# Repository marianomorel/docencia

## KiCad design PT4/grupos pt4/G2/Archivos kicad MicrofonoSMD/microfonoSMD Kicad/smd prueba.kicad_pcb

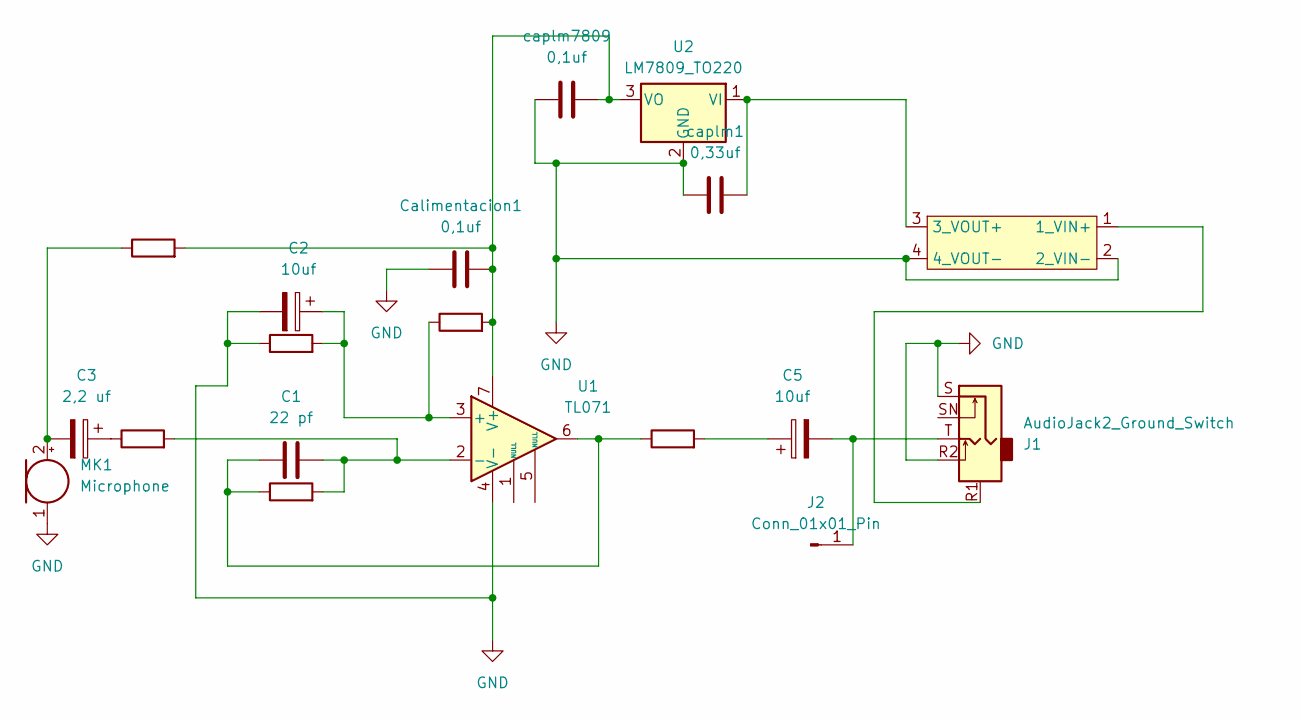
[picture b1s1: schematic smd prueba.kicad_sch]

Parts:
C1: 22 pf; C_0805_2012Metric_Pad1.18x1.45mm_HandSolder
C2, C5: 10uf; CP_Elec_4x5.4
C3: 2,2 uf; CP_Elec_4x5.4
Calimentacion1: 0,1uf; C_0805_2012Metric_Pad1.18x1.45mm_HandSolder
J1: AudioJack2_Ground_Switch; Jack_3.5mm_PJ320D_Horizontal
J2: Conn_01x01_Pin; PinHeader_1x01_P1.00mm_Vertical
MK1: Microphone; POM-2244P-C3310-2-R
R3: 2,2k; R_1206_3216Metric_Pad1.30x1.75mm_HandSolder
R5: 100; R_1206_3216Metric_Pad1.30x1.75mm_HandSolder
RP2: 200k; R_1206_3216Metric_Pad1.30x1.75mm_HandSolder
RP3: 10k; R_1206_3216Metric_Pad1.30x1.75mm_HandSolder
Ralimentacion1: 10k; R_1206_3216Metric_Pad1.30x1.75mm_HandSolder
Rpolarizadordeelectret1: 10k; R_1206_3216Metric_Pad1.30x1.75mm_HandSolder
U1: TL071; soic 8 personalizado
U2: LM7809_TO220; TO-252-2
U3: modulo mt3608
caplm1: 0,33uf; C_0805_2012Metric_Pad1.18x1.45mm_HandSolder
caplm7809: 0,1uf; C_0805_2012Metric_Pad1.18x1.45mm_HandSolder

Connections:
GND: C2.2, Calimentacion1.1, J1.R2, J1.S, MK1.1 (-), RP3.1, U1.4 (V-), U2.2 (GND), U3.2 (2_VIN-), U3.4 (4_VOUT-), caplm1.1, caplm7809.1
unnamed: C1.2, R5.1, RP2.1, U1.6
unnamed: C3.1, R3.1
unnamed: C5.1, R5.2
unnamed: C5.2, J1.T, J2.1
unnamed: C3.2, MK1.2 (+), Rpolarizadordeelectret1.1
unnamed: C2.1, RP3.2, Ralimentacion1.1, U1.3 (+)
unnamed: C1.1, R3.2, RP2.2, U1.2 (-)
unnamed: Calimentacion1.2, Ralimentacion1.2, Rpolarizadordeelectret1.2, U1.7 (V+), U2.3 (VO), caplm7809.2
unnamed: U2.1 (VI), U3.3 (3_VOUT+), caplm1.2
unnamed: J1.R1, U3.1 (1_VIN+)

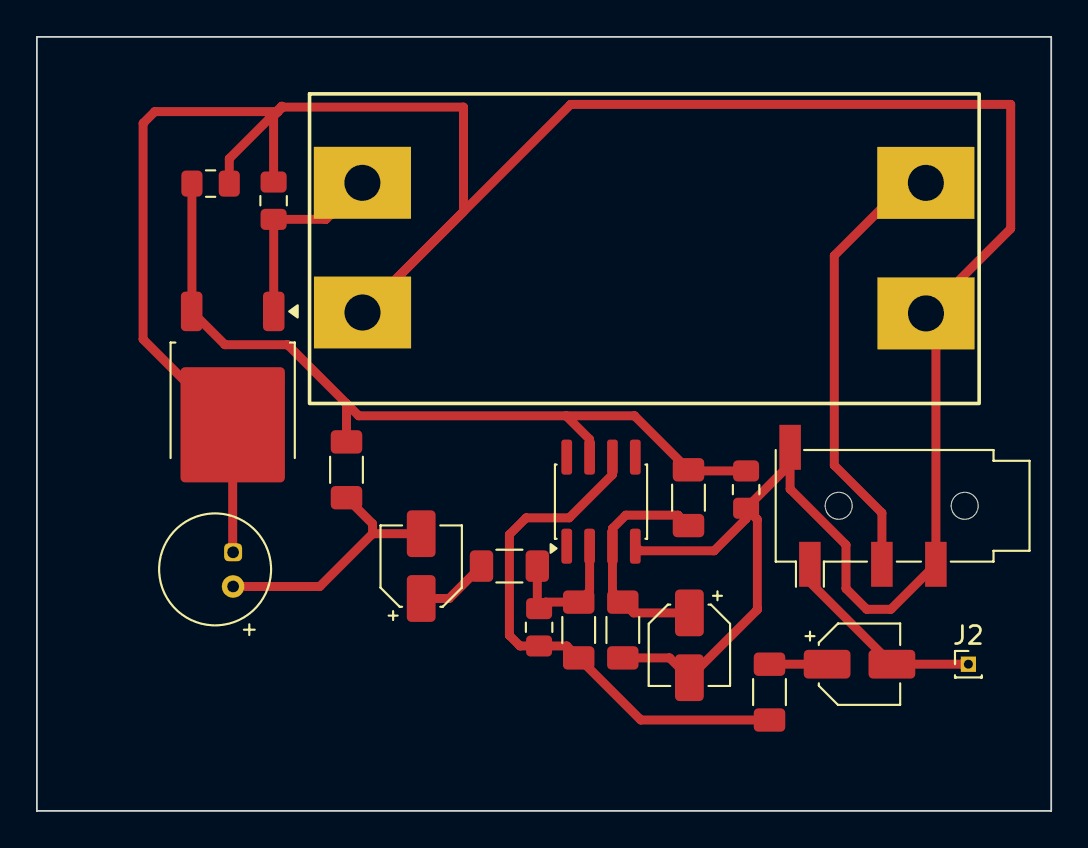
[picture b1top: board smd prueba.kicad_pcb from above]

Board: 2 copper layers, 56.3 x 43.0 mm, 19 parts (0 on the bottom side), 11 nets.

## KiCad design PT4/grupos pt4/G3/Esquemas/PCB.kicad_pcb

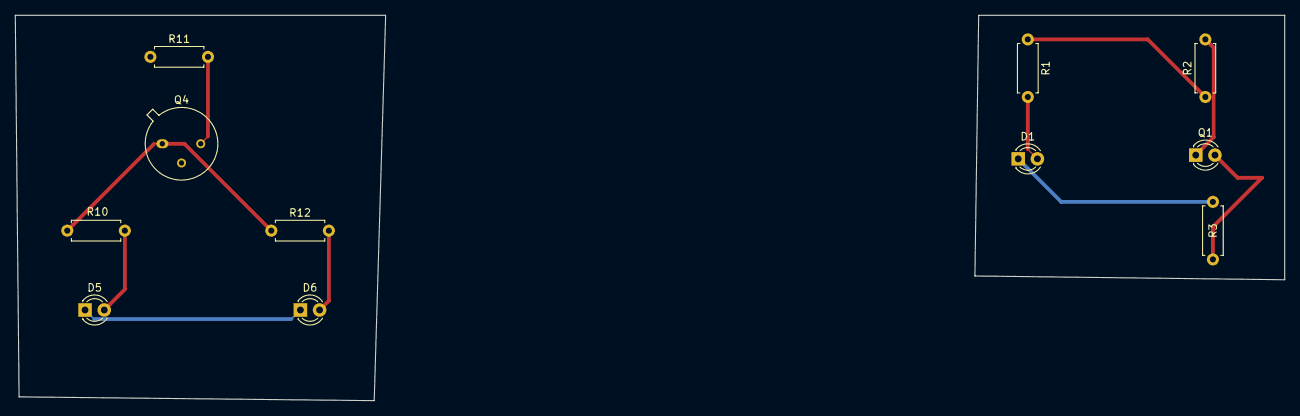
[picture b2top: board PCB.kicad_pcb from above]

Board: 2 copper layers, 168.0 x 51.0 mm, 11 parts (0 on the bottom side), 9 nets.

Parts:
D1, D5, D6: IR204A; LED_D3.0mm_IRBlack
Q1: TEPT4400; LED_D3.0mm_Clear
Q4: 2N2219; TO-39-3
R1, R2, R10, R12: 220; R_Axial_DIN0207_L6.3mm_D2.5mm_P7.62mm_Horizontal
R3, R11: 10k; R_Axial_DIN0207_L6.3mm_D2.5mm_P7.62mm_Horizontal

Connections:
+5V: R1.1, R2.1, R11.1
GND: D1.1 (K), D5.1 (K), D6.1 (K), R3.2
unnamed: Q1.2 (E), R3.1
unnamed: D1.2 (A), R1.2
unnamed: D5.2 (A), R10.2
unnamed: D6.2 (A), R12.2
unnamed: Q1.1 (C), R2.2
unnamed: Q4.3 (C), R11.2
unnamed: Q4.1 (E), R10.1, R12.1

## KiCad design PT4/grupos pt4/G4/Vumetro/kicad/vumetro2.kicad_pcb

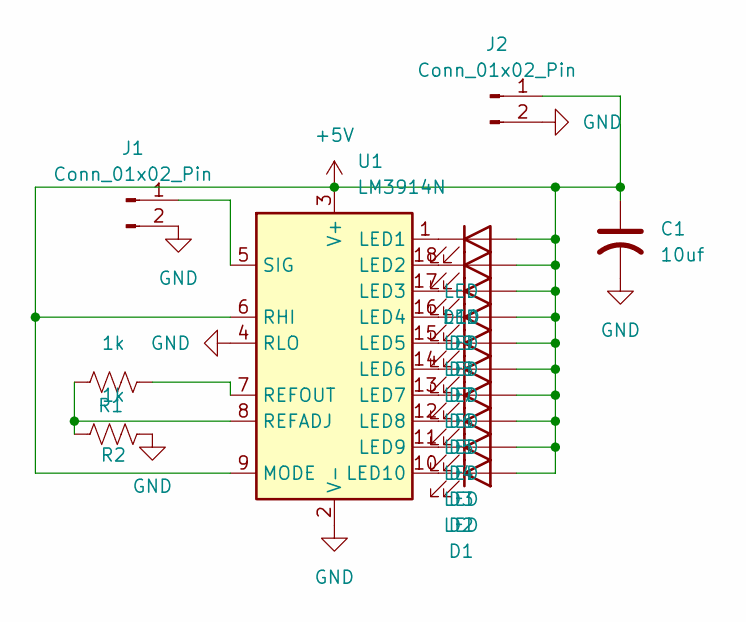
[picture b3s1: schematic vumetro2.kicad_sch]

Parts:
C1: 10uf; CP_Radial_D5.0mm_P2.00mm
D1, D2, D3, D4, D5, D6, D7, D8, D9, D10: LED; LED_D3.0mm_FlatTop
J1, J2: Conn_01x02_Pin; TerminalBlock_4Ucon_1x02_P3.50mm_Horizontal
R1, R2: 1k; R_Axial_DIN0204_L3.6mm_D1.6mm_P5.08mm_Horizontal
U1: LM3914N; DIP-18_W7.62mm

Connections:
+5V: C1.1, D1.2 (A), D2.2 (A), D3.2 (A), D4.2 (A), D5.2 (A), D6.2 (A), D7.2 (A), D8.2 (A), D9.2 (A), D10.2 (A), J2.1, U1.3 (V+), U1.6 (RHI), U1.9 (MODE)
GND: C1.2, J1.2, J2.2, R2.2, U1.2 (V-), U1.4 (RLO)
unnamed: D1.1 (K), U1.10 (LED10)
unnamed: D2.1 (K), U1.11 (LED9)
unnamed: D3.1 (K), U1.12 (LED8)
unnamed: D4.1 (K), U1.13 (LED7)
unnamed: D5.1 (K), U1.14 (LED6)
unnamed: D6.1 (K), U1.15 (LED5)
unnamed: D7.1 (K), U1.16 (LED4)
unnamed: D8.1 (K), U1.17 (LED3)
unnamed: D9.1 (K), U1.18 (LED2)
unnamed: D10.1 (K), U1.1 (LED1)
unnamed: J1.1, U1.5 (SIG)
unnamed: R1.1, R2.1, U1.8 (REFADJ)
unnamed: R1.2, U1.7 (REFOUT)

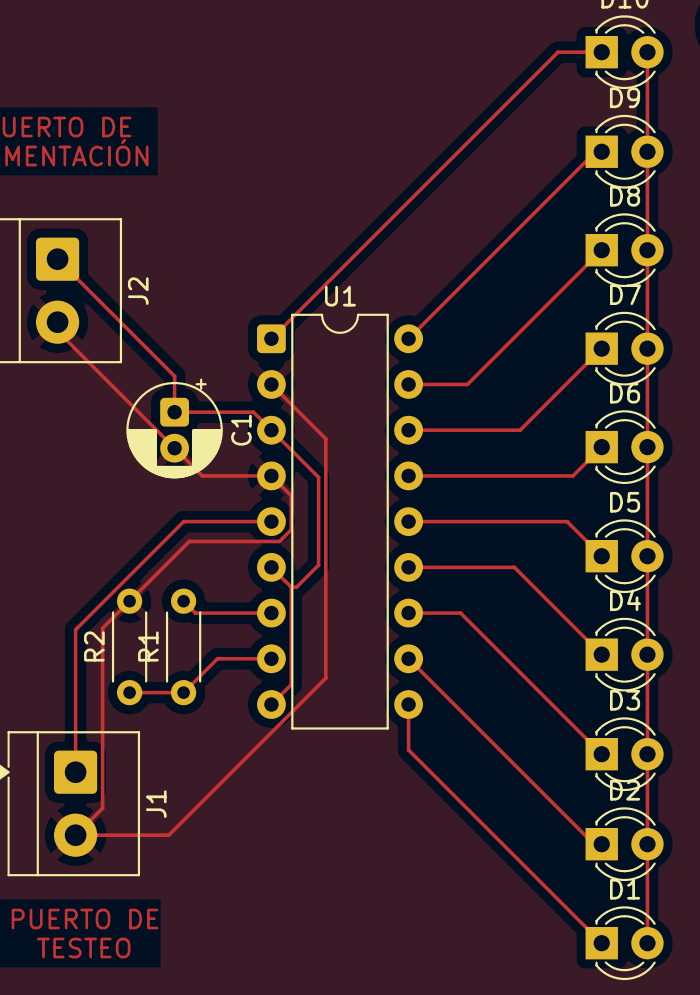
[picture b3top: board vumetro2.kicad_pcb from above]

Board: 2 copper layers, 16 parts (0 on the bottom side), 15 nets.

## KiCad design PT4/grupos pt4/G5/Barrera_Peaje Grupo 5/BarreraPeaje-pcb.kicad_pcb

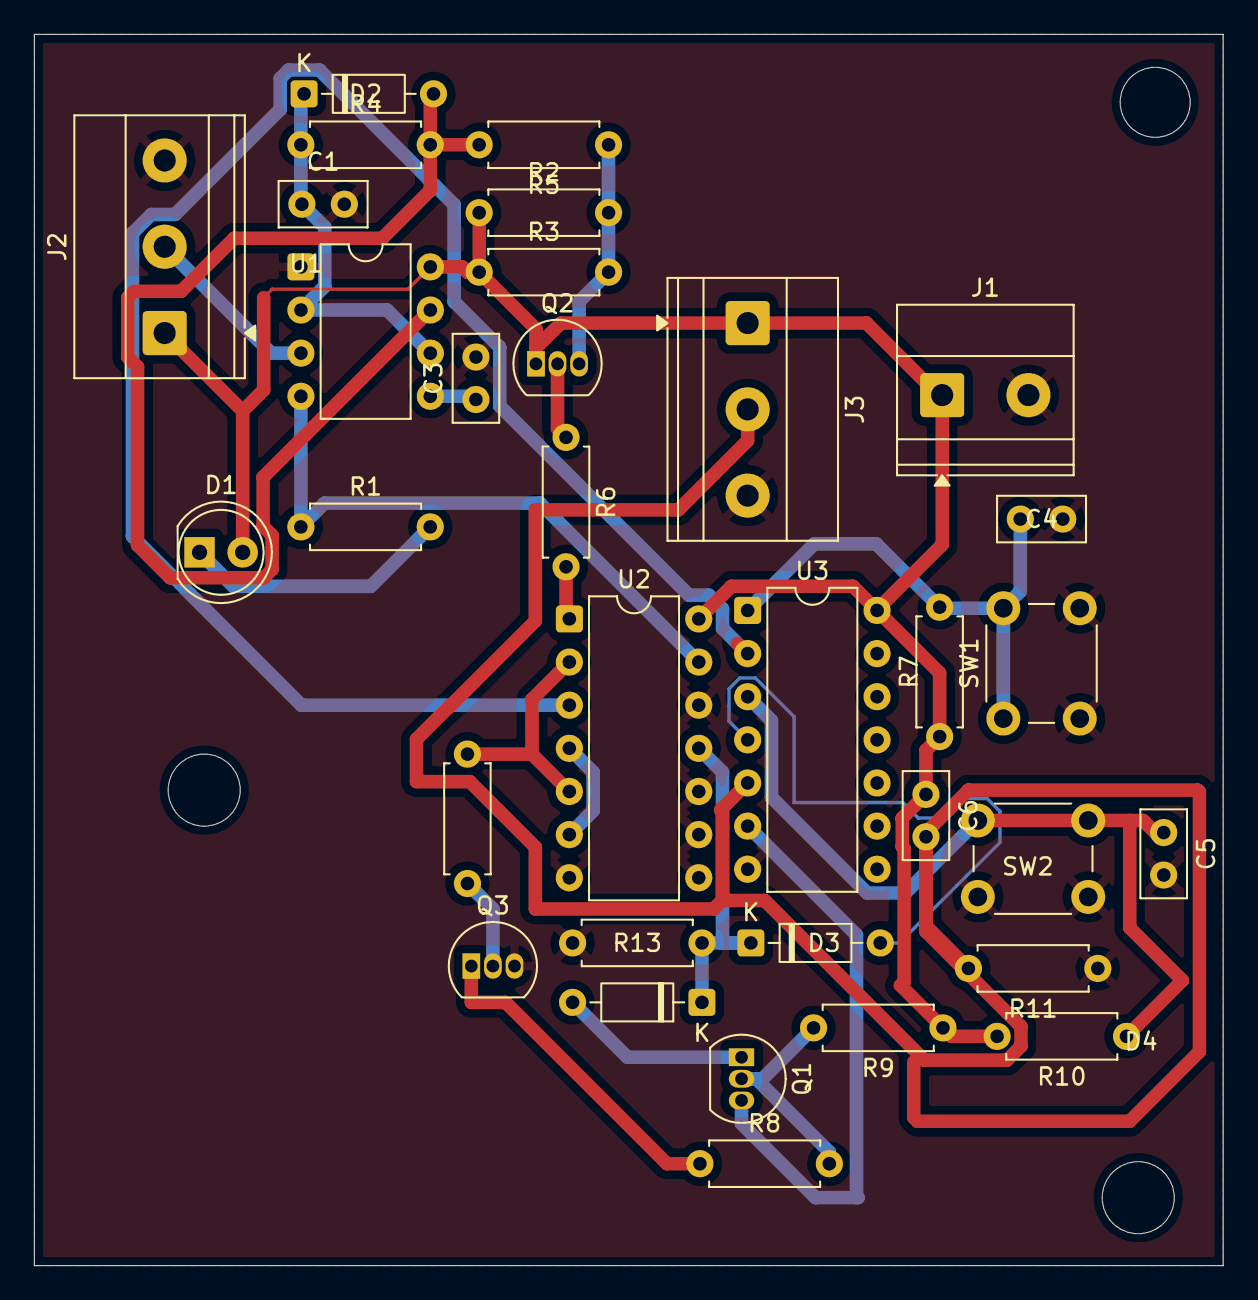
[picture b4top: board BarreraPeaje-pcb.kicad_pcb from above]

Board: 2 copper layers, 70.0 x 72.5 mm, 33 parts (0 on the bottom side), 24 nets.

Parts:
C1: 10nF; C_Disc_D5.0mm_W2.5mm_P2.50mm
C3, C4, C5, C6: 100nF; C_Disc_D5.0mm_W2.5mm_P2.50mm
D1: LED; LED_D5.0mm
D2, D3, D4: 1N4148; D_DO-35_SOD27_P7.62mm_Horizontal
J1: Alimentacion 12V; TerminalBlock_Phoenix_MKDS-1,5-2-5.08_1x02_P5.08mm_Horizont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
J2: Salida/Servo; TerminalBlock_Phoenix_MKDS-1,5-3-5.08_1x03_P5.08mm_Horizont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
J3: Sensor en Barrera; TerminalBlock_Phoenix_MKDS-1,5-3-5.08_1x03_P5.08mm_Horizont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
Q1: BC558; TO-92_Inline
Q2, Q3: BC548; TO-92_Inline
R1, R6, R7, R10, R11, R13: 10k; R_Axial_DIN0207_L6.3mm_D2.5mm_P7.62mm_Horizontal
R2: 47k; R_Axial_DIN0207_L6.3mm_D2.5mm_P7.62mm_Horizontal
R3, R9: 15k; R_Axial_DIN0207_L6.3mm_D2.5mm_P7.62mm_Horizontal
R4: 270k; R_Axial_DIN0207_L6.3mm_D2.5mm_P7.62mm_Horizontal
R5: 180; R_Axial_DIN0207_L6.3mm_D2.5mm_P7.62mm_Horizontal
R8, R12: 1k; R_Axial_DIN0207_L6.3mm_D2.5mm_P7.62mm_Horizontal
SW1: Open/Close; SW_PUSH_6mm_H4.3mm
SW2: Marcha/Stop; SW_PUSH_6mm_H4.3mm
U1: LM555xN; DIP-8_W7.62mm
U2: 4013; DIP-14_W7.62mm
U3: 40106; DIP-14_W7.62mm

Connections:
+5V: C6.1, D1.2 (A), J1.1, J2.1, J3.1, Q2.1 (C), R2.1, R3.1, R7.1, R9.1, R10.2, U1.8 (VCC), U2.14 (VDD), U3.14 (VDD)
GND: C1.2, C3.2, C4.2, C5.2, J1.2, J2.3, J3.3, Q3.3 (E), R11.1, R13.2, SW1.2, SW2.1, U1.1 (GND), U2.7 (VSS), U2.8 (S), U2.9 (D), U2.10 (R), U2.12 (~Q), U3.7 (VSS)
unnamed: C4.1, R7.2, SW1.1, U3.1
unnamed: C5.1, R10.1, SW2.2, U3.3
unnamed: D1.1 (K), R1.2
unnamed: D2.2 (A), R4.2, R5.2, U1.7 (DIS)
unnamed: C1.1, D2.1 (K), R4.1, U1.2 (TR), U1.6 (THR)
unnamed: D3.2 (A), U3.4
unnamed: D3.1 (K), D4.1 (K), R13.1, U2.11 (C)
unnamed: D4.2 (A), Q1.1 (C)
unnamed: J2.2, U1.3 (Q)
unnamed: C6.2, J3.2, R11.2, U3.5
unnamed: Q1.2 (B), R8.2, R9.2
unnamed: Q1.3 (E), U3.6
unnamed: Q2.2 (B), R6.1
unnamed: Q2.3 (E), R2.2, R3.2, R5.1
unnamed: Q3.2 (B), R12.2
unnamed: Q3.1 (C), R8.1
unnamed: C3.1, U1.5 (CV)
unnamed: R1.1, U1.4 (R), U2.13 (Q)
unnamed: U2.3 (C), U3.2
unnamed: R12.1, U2.2 (~Q), U2.5 (D)
unnamed: R6.2, U2.1 (Q)
unnamed: U2.4 (R), U2.6 (S)

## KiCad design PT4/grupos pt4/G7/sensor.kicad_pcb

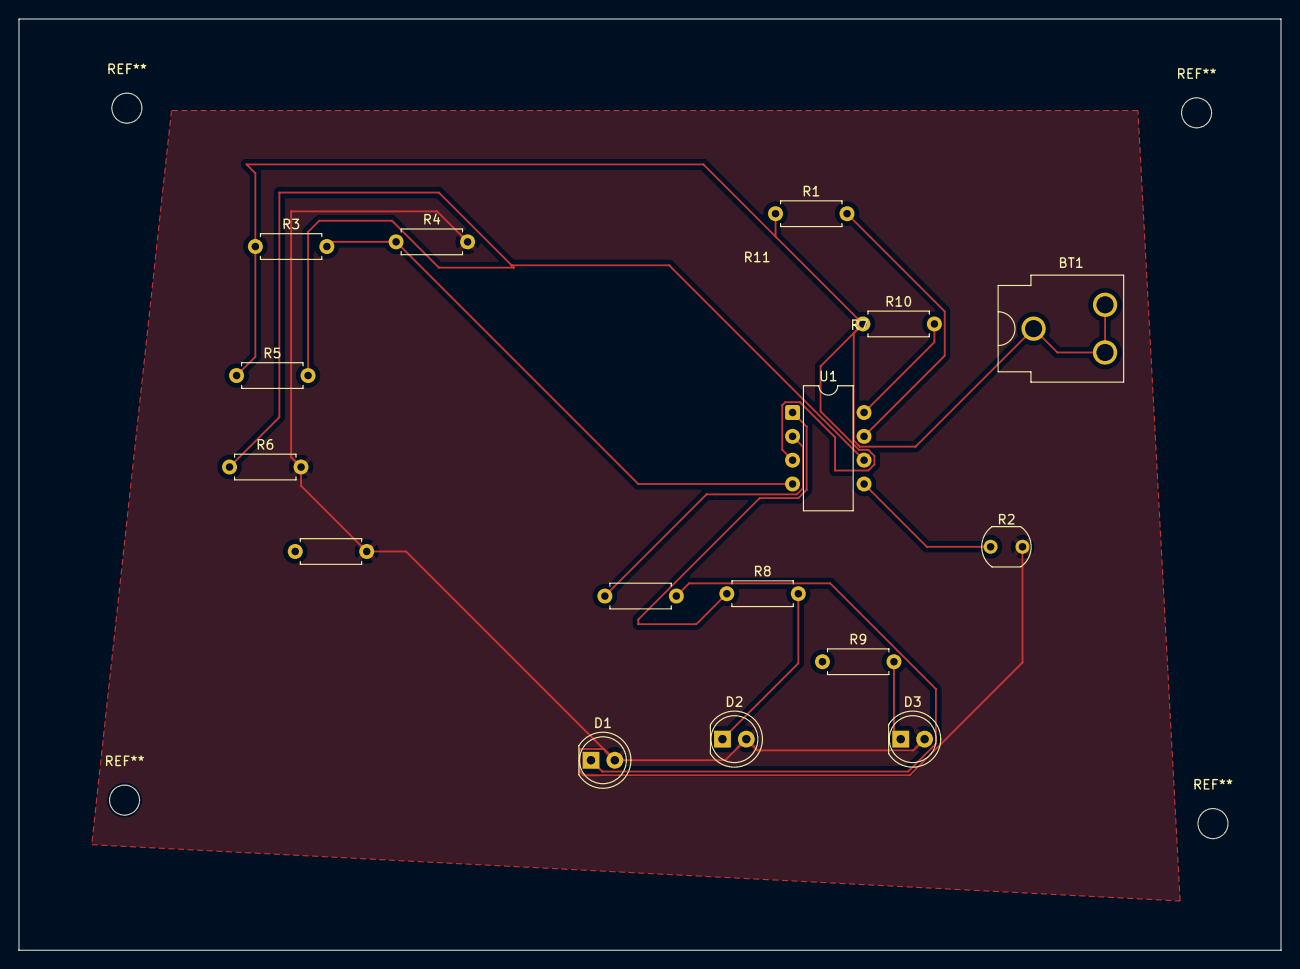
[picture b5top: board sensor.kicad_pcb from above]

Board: 2 copper layers, 134.5 x 99.2 mm, 16 parts (0 on the bottom side), 11 nets.

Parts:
BT1: Battery; BatteryClip_Keystone_54_D16-19mm
D1, D2, D3: LED; LED_D5.0mm
R1, R3, R4, R5, R6, R7, R8, R9, R10, R11: R; R_Axial_DIN0207_L6.3mm_D2.5mm_P7.62mm_Horizontal
R2: LDR07; R_LDR_5.1x4.3mm_P3.4mm_Vertical
U1: LM339; CERDIP-8_W7.62mm_SideBrazed

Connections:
Earth: D1.2 (A), D2.2 (A), D3.2 (A), R2.2, R4.2, R6.2, R11.2
unnamed: BT1.1 (+), R1.1, R3.1, R5.1, R10.1, U1.3 (V+)
unnamed: D1.1 (K), R7.2
unnamed: D2.1 (K), R8.2
unnamed: D3.1 (K), R9.2
unnamed: R7.1, U1.2
unnamed: R8.1, U1.1
unnamed: R1.2, R2.1, U1.5 (+), U1.7 (+)
unnamed: R3.2, R4.1, U1.4 (-)
unnamed: R5.2, R6.1, U1.6 (-)
unnamed: R10.2, U1.8 (-)

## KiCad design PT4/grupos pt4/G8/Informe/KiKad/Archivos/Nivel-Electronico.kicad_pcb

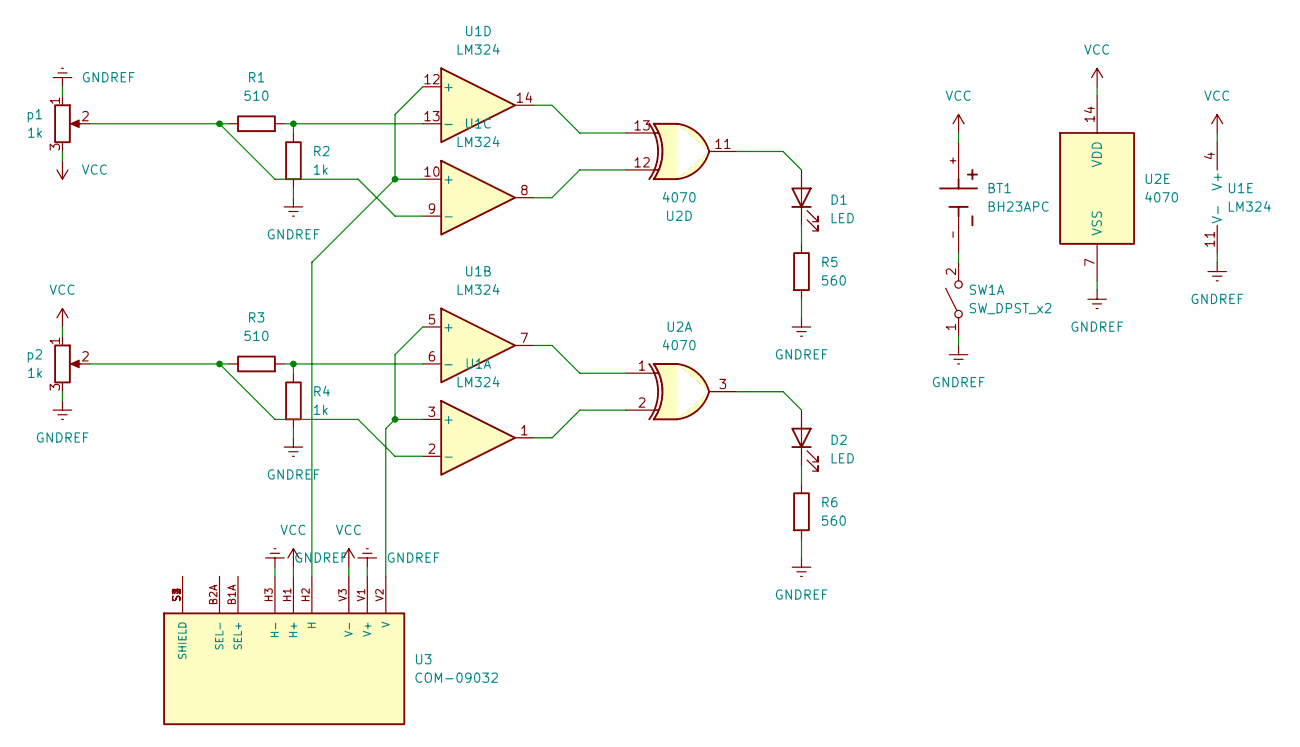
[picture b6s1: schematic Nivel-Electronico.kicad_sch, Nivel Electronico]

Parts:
BT1: BH23APC; BAT_BH23APC
D1, D2: LED; LED_D5.0mm
R1, R3: 510; R_Axial_DIN0204_L3.6mm_D1.6mm_P5.08mm_Vertical
R2, R4: 1k; R_Axial_DIN0204_L3.6mm_D1.6mm_P5.08mm_Vertical
R5, R6: 560; R_Axial_DIN0204_L3.6mm_D1.6mm_P5.08mm_Vertical
SW1: SW_DPST_x2; SW_Push_2P2T_Toggle_CK_PVA2OAH5xxxxxxV2
U1: LM324; DIP-14_W7.62mm_LongPads
U2: 4070; DIP-14_W7.62mm_LongPads
U3: COM-09032; XDCR_COM-09032
p1, p2: 1k; Potentiometer_ACP_CA9-V10_Vertical

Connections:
GNDREF: R2.2, R4.2, R5.2, R6.2, SW1.1 (A), U1.11 (V-), U2.7 (VSS), U3.H3 (H-), U3.V1 (V+), p1.1, p2.3
unnamed: D1.2 (A), U2.11
unnamed: D1.1 (K), R5.1
unnamed: D2.2 (A), U2.3
unnamed: D2.1 (K), R6.1
unnamed: BT1.-, SW1.2 (B)
unnamed: U1.1, U2.2
unnamed: U1.7, U2.1
unnamed: U1.8, U2.12
unnamed: U1.14, U2.13
unnamed: U1.3 (+), U1.5 (+), U3.V2 (V)
unnamed: R3.1, U1.2 (-), p2.2
unnamed: R3.2, R4.1, U1.6 (-)
unnamed: U1.10 (+), U1.12 (+), U3.H2 (H)
unnamed: R1.1, U1.9 (-), p1.2
unnamed: R1.2, R2.1, U1.13 (-)
unnamed: U3.S1 (SHIELD), U3.S2 (SHIELD), U3.S3 (SHIELD), U3.S4 (SHIELD)
VCC: BT1.+, U1.4 (V+), U2.14 (VDD), U3.H1 (H+), U3.V3 (V-), p1.3, p2.1

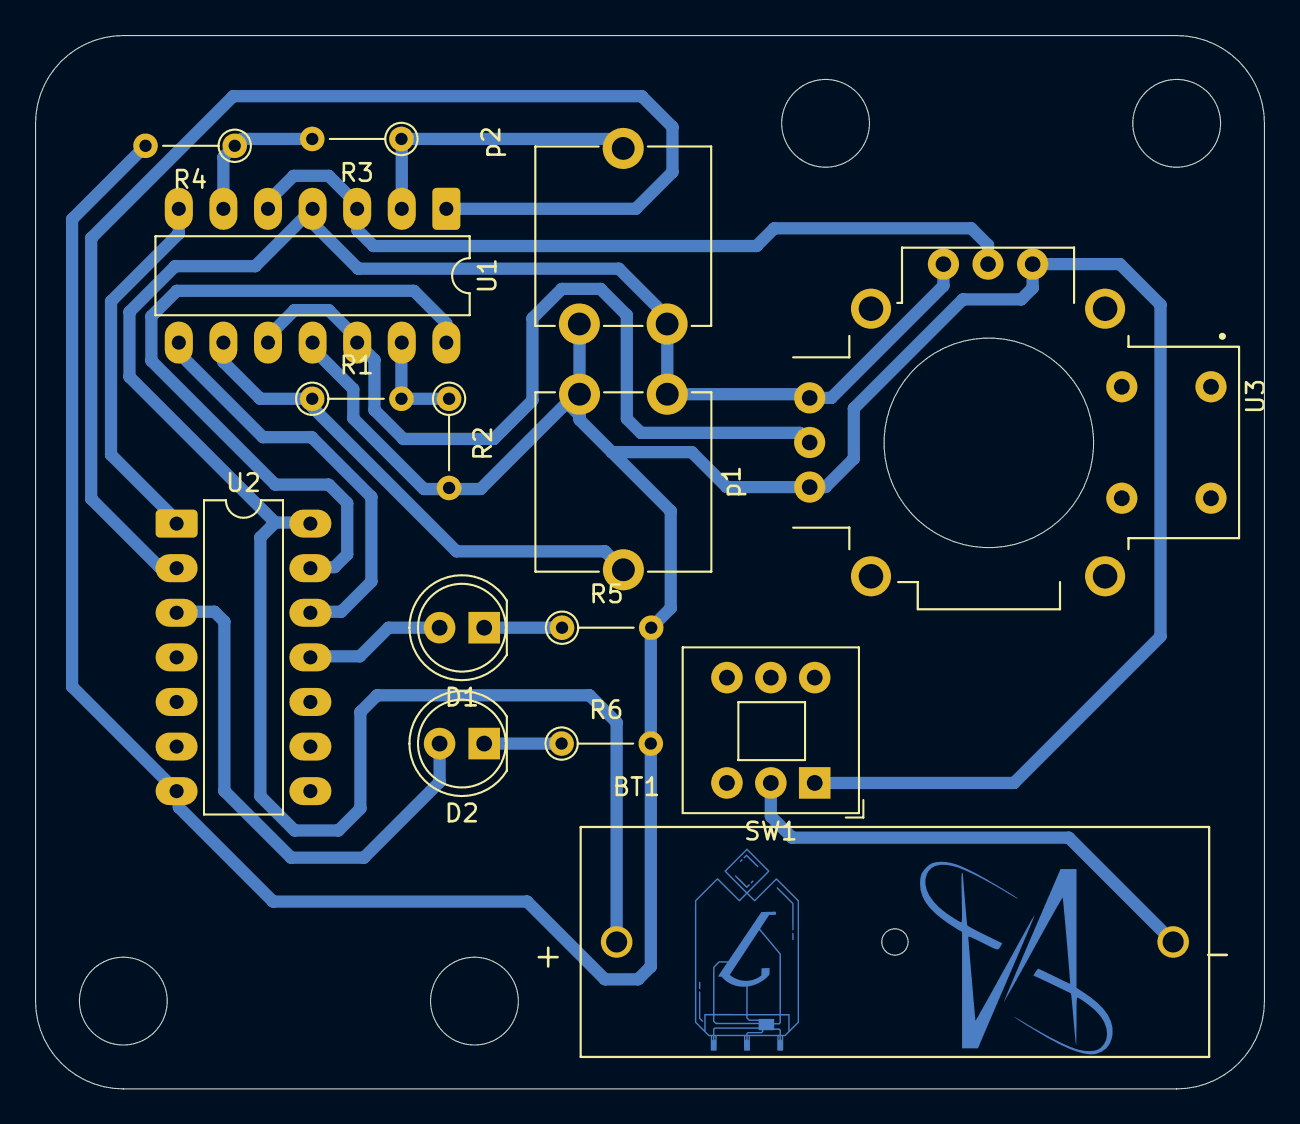
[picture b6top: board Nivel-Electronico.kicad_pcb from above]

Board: 2 copper layers, 70.0 x 60.0 mm, 15 parts (0 on the bottom side), 18 nets.

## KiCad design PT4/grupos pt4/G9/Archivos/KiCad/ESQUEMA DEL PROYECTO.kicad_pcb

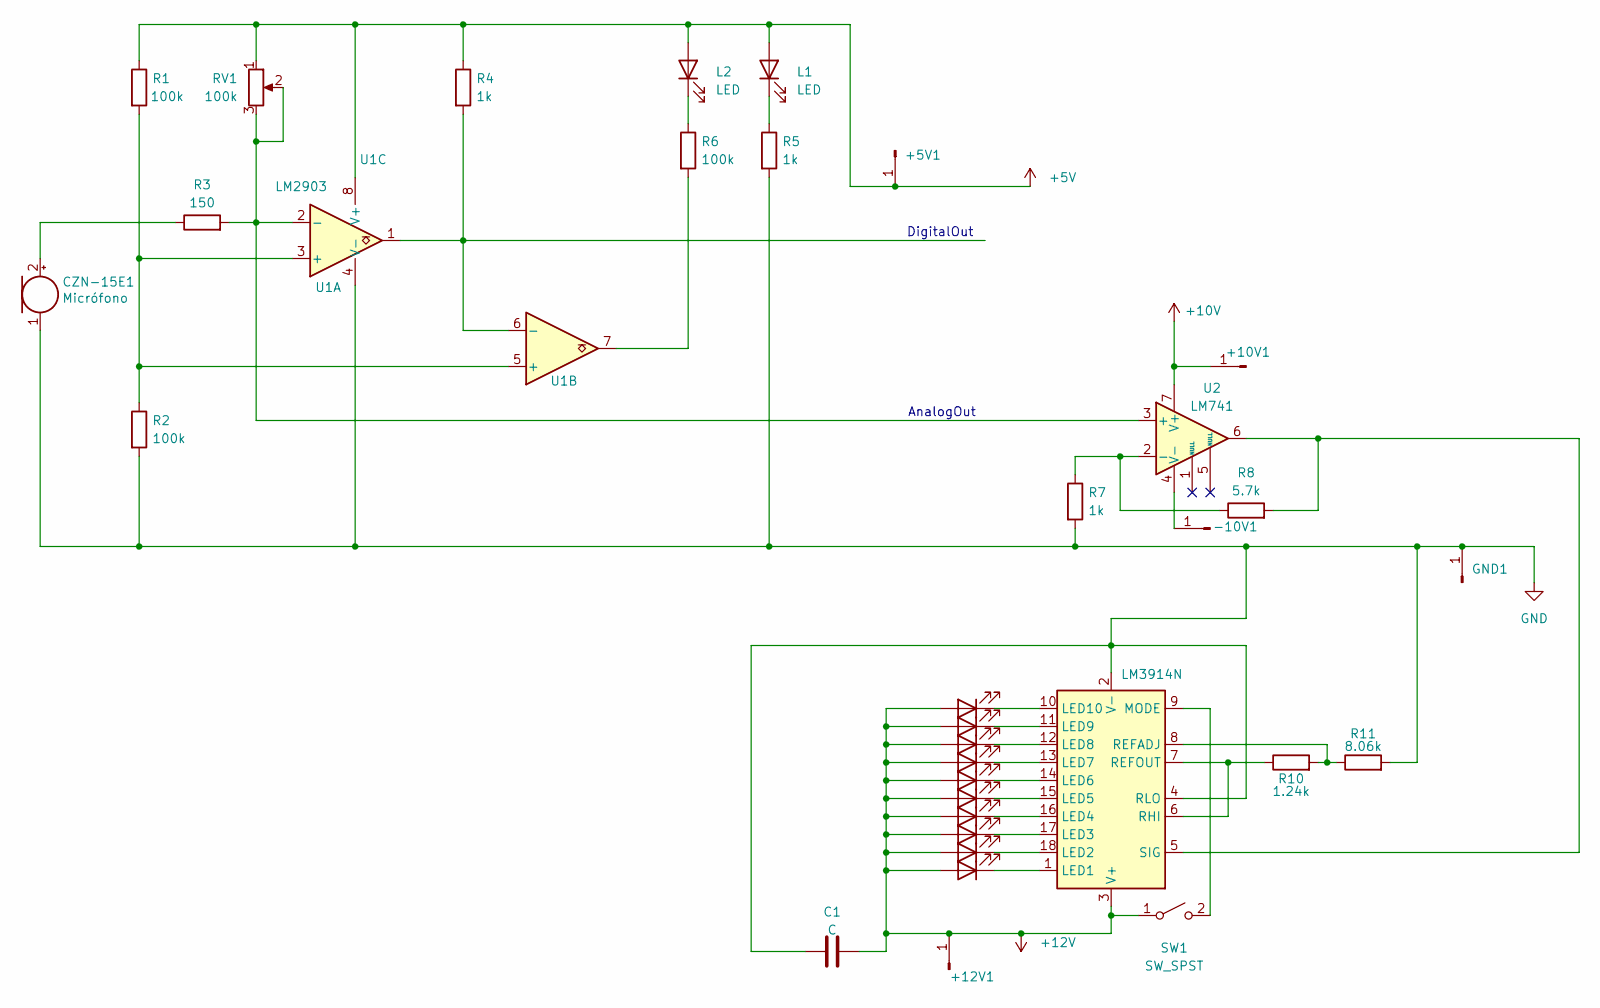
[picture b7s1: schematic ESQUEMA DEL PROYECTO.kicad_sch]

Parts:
+5V1, +10V1, +12V1: Conn_01x01_Pin; TestPoint_Pad_D3.0mm
-10V1: Conn_01x01_Pin; TestPoint_Pad_D3.0mm
C1: C; CP_EIA-1608-08_AVX-J
CZN-15E1: Micrófono; POM-2244P-C3310-2-R
GND1: Conn_01x01_Pin; TestPoint_Pad_D3.0mm
L1, L2, L3, L4, L5, L6, L7, L8, L9, L10, L11, L12: LED; LED_0603_1608Metric
R1, R2, R6: 100k; R_0805_2012Metric
R3: 150; R_0805_2012Metric
R4, R5, R7: 1k; R_0805_2012Metric
R8: 5.7k; R_0805_2012Metric
R10: 1.24k; R_0805_2012Metric
R11: 8.06k; R_0805_2012Metric
RV1: 100k; Potentiometer_Bourns_3296X_Horizontal
SW1: SW_SPST; SW_SPST_TL3342
U1: LM2903; DIP-8_W7.62mm
U2: LM741; DIP-8_W7.62mm
U3: LM3914N; DIP-18_W7.62mm

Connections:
+5V: +5V1.1, L1.2 (A), L2.2 (A), R1.1, R4.1, RV1.1, U1.8 (V+)
+10V: +10V1.1, U2.7 (V+)
+12V: +12V1.1, C1.2, L3.2 (A), L4.2 (A), L5.2 (A), L6.2 (A), L7.2 (A), L8.2 (A), L9.2 (A), L10.2 (A), L11.2 (A), L12.2 (A), SW1.1 (A), U3.3 (V+)
GND: C1.1, CZN-15E1.1 (-), GND1.1, R2.2, R5.2, R7.2, R11.2, U1.4 (V-), U3.2 (V-), U3.4 (RLO)
unnamed: -10V1.1, U2.4 (V-)
unnamed: CZN-15E1.2 (+), R3.1
unnamed: L1.1 (K), R5.1
unnamed: L2.1 (K), R6.1
unnamed: L3.1 (K), U3.1 (LED1)
unnamed: L4.1 (K), U3.18 (LED2)
unnamed: L5.1 (K), U3.17 (LED3)
unnamed: L6.1 (K), U3.16 (LED4)
unnamed: L7.1 (K), U3.15 (LED5)
unnamed: L8.1 (K), U3.14 (LED6)
unnamed: L9.1 (K), U3.13 (LED7)
unnamed: L10.1 (K), U3.12 (LED8)
unnamed: L11.1 (K), U3.11 (LED9)
unnamed: L12.1 (K), U3.10 (LED10)
unnamed: R6.2, U1.7
unnamed: SW1.2 (B), U3.9 (MODE)
unnamed: R1.2, R2.1, U1.3 (+), U1.5 (+)
unnamed: R3.2, RV1.2, RV1.3, U1.2 (-), U2.3 (+)
unnamed: R4.2, U1.1, U1.6 (-)
unnamed: R7.1, R8.1, U2.2 (-)
unnamed: R10.2, R11.1, U3.8 (REFADJ)
unnamed: R10.1, U3.6 (RHI), U3.7 (REFOUT)
unnamed: R8.2, U2.6, U3.5 (SIG)

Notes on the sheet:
AnalogOut
DigitalOut

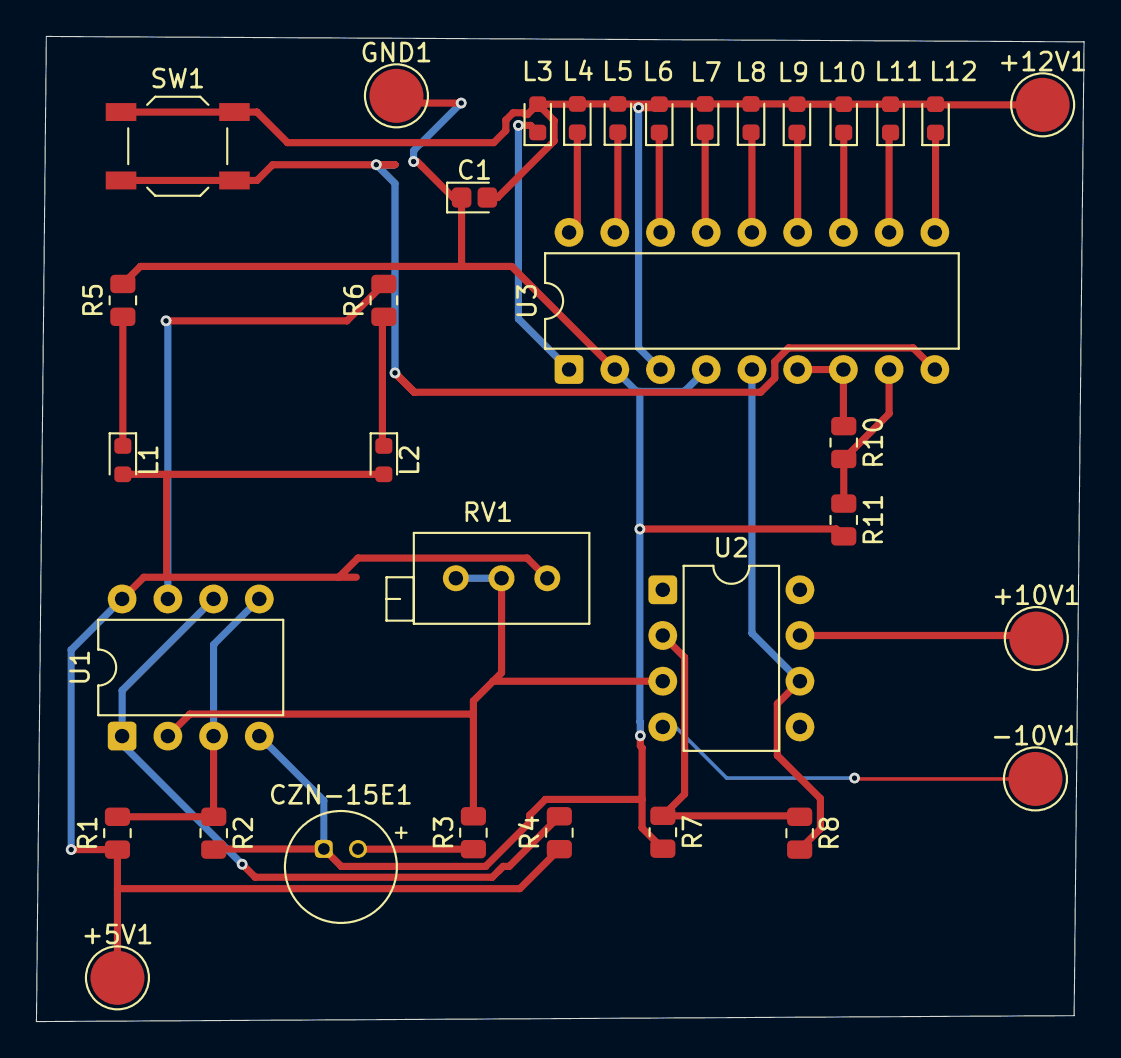
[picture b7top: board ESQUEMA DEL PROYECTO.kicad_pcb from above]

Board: 2 copper layers, 58.2 x 54.7 mm, 34 parts (0 on the bottom side), 27 nets.
